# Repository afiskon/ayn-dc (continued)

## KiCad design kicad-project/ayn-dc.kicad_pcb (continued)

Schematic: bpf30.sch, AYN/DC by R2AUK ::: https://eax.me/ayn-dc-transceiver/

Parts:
C65: 1-10p; C_Trim_THD_L7.0mm_W6.5mm_P5.00mm
C66, C69: 100p; C_0805_2012Metric_Pad1.15x1.40mm_HandSolder
C67, C68: 1-30p; C_Trim_THD_L7.0mm_W6.5mm_P5.00mm
D8, D9: 1N4148W; D_SOD-123
K4, K5: G6K-2F-Y; Relay_DPDT_Omron_G6K-2F-Y
Q9: MMBT3904; SOT-23
R67: 4.7K; R_0805_2012Metric_Pad1.15x1.40mm_HandSolder
T6, T7: T37-6; DIP-4_W7.62mm

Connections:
+12V: D8.1 (K), D9.1 (K), K4.1, K5.1; also elsewhere on the board
BPFS: K4.3; also elsewhere on the board
CTL30: R67.2; also elsewhere on the board
GND: C66.2, C67.2, C68.2, C69.2, K4.5, K4.6, K4.7, K5.5, K5.6, K5.7, Q9.2 (E), T6.3, T6.4, T7.3, T7.4; also elsewhere on the board
GND30: D8.2 (A), D9.2 (A), K4.8, K5.8, Q9.3 (C)
unnamed: C65.1, C68.1, C69.1, T7.1
unnamed: C65.2, C66.1, C67.1, T6.2
unnamed: K4.4, T6.1
unnamed: K5.4, T7.2
unnamed: Q9.1 (B), R67.1
SWR_BRIDGE: K5.3; also elsewhere on the board

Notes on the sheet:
5:25T @ T37-6
25:5T @ T37-6

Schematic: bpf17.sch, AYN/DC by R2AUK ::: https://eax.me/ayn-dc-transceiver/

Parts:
C70: 1-10p; C_Trim_THD_L7.0mm_W6.5mm_P5.00mm
C71, C74: 47p; C_0805_2012Metric_Pad1.15x1.40mm_HandSolder
C72, C73: 1-30p; C_Trim_THD_L7.0mm_W6.5mm_P5.00mm
D10, D11: 1N4148W; D_SOD-123
K6, K7: G6K-2F-Y; Relay_DPDT_Omron_G6K-2F-Y
Q10: MMBT3904; SOT-23
R68: 4.7K; R_0805_2012Metric_Pad1.15x1.40mm_HandSolder
T8, T9: T37-6; DIP-4_W7.62mm

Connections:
+12V: D10.1 (K), D11.1 (K), K6.1, K7.1; also elsewhere on the board
BPFS: K6.3; also elsewhere on the board
CTL17: R68.2; also elsewhere on the board
GND: C71.2, C72.2, C73.2, C74.2, K6.5, K6.6, K6.7, K7.5, K7.6, K7.7, Q10.2 (E), T8.3, T8.4, T9.3, T9.4; also elsewhere on the board
GND17: D10.2 (A), D11.2 (A), K6.8, K7.8, Q10.3 (C)
unnamed: C70.1, C73.1, C74.1, T9.1
unnamed: C70.2, C71.1, C72.1, T8.2
unnamed: K6.4, T8.1
unnamed: K7.4, T9.2
unnamed: Q10.1 (B), R68.1
SWR_BRIDGE: K7.3; also elsewhere on the board

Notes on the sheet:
3:19T @ T37-6
19:3T @ T37-6

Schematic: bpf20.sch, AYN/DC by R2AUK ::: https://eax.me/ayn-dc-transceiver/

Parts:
C75: 1-10p; C_Trim_THD_L7.0mm_W6.5mm_P5.00mm
C76, C79: 68p; C_0805_2012Metric_Pad1.15x1.40mm_HandSolder
C77, C78: 1-30p; C_Trim_THD_L7.0mm_W6.5mm_P5.00mm
D12, D13: 1N4148W; D_SOD-123
K8, K9: G6K-2F-Y; Relay_DPDT_Omron_G6K-2F-Y
Q11: MMBT3904; SOT-23
R69: 4.7K; R_0805_2012Metric_Pad1.15x1.40mm_HandSolder
T10, T11: T37-6; DIP-4_W7.62mm

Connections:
+12V: D12.1 (K), D13.1 (K), K8.1, K9.1; also elsewhere on the board
BPFS: K8.3; also elsewhere on the board
CTL20: R69.2; also elsewhere on the board
GND: C76.2, C77.2, C78.2, C79.2, K8.5, K8.6, K8.7, K9.5, K9.6, K9.7, Q11.2 (E), T10.3, T10.4, T11.3, T11.4; also elsewhere on the board
GND20: D12.2 (A), D13.2 (A), K8.8, K9.8, Q11.3 (C)
unnamed: C75.1, C78.1, C79.1, T11.1
unnamed: C75.2, C76.1, C77.1, T10.2
unnamed: K8.4, T10.1
unnamed: K9.4, T11.2
unnamed: Q11.1 (B), R69.1
SWR_BRIDGE: K9.3; also elsewhere on the board

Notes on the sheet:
4:21T @ T37-6
21:4T @ T37-6

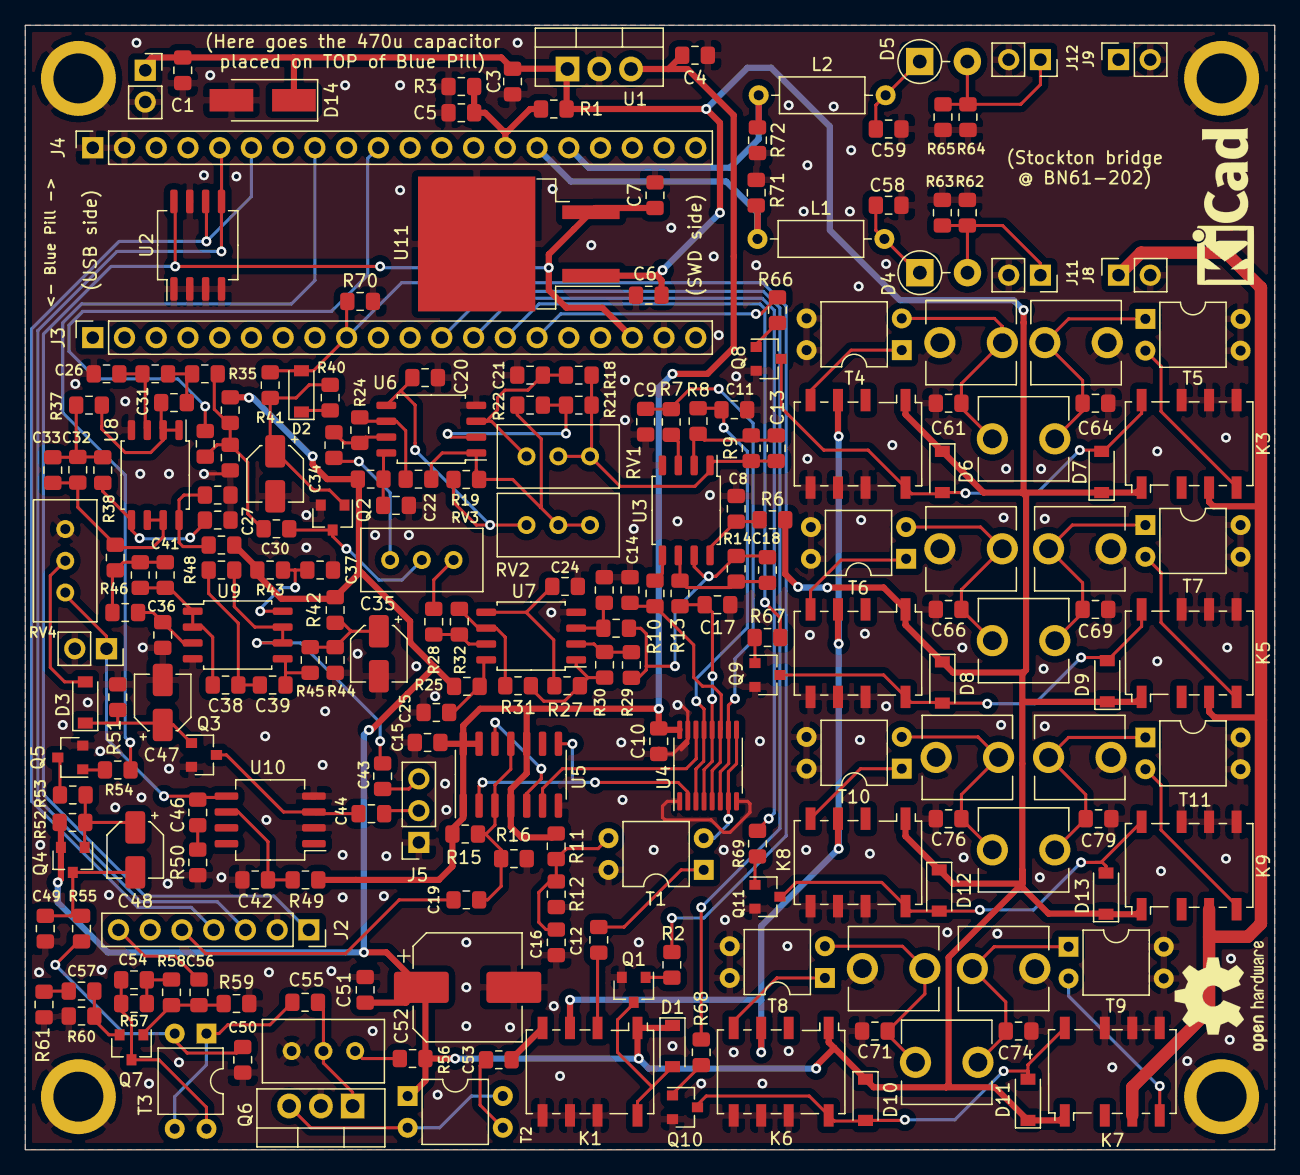
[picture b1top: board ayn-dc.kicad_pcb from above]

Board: 2 copper layers, 100.0 x 90.0 mm, 226 parts (0 on the bottom side), 128 nets.

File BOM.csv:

Reference, Quantity, Value, Footprint
C13 C18 C21 C58 C59 ,5,0.01u,Capacitor_SMD:C_0805_2012Metric_Pad1.15x1.40mm_HandSolder
C2 ,1,470u,Connector_PinSocket_2.54mm:PinSocket_1x02_P2.54mm_Vertical
C23 C31 C46 ,3,0.047u,Capacitor_SMD:C_0805_2012Metric_Pad1.15x1.40mm_HandSolder
C26 C27 C36 ,3,1000p,Capacitor_SMD:C_0805_2012Metric_Pad1.15x1.40mm_HandSolder
C29 C66 C69 ,3,100p,Capacitor_SMD:C_0805_2012Metric_Pad1.15x1.40mm_HandSolder
C3 C6 C24 ,3,0.47u,Capacitor_SMD:C_0805_2012Metric_Pad1.15x1.40mm_HandSolder
C32 C40 ,2,0.033u,Capacitor_SMD:C_0805_2012Metric_Pad1.15x1.40mm_HandSolder
C33 C38 C39 ,3,2200p,Capacitor_SMD:C_0805_2012Metric_Pad1.15x1.40mm_HandSolder
C34 ,1,4.7u,Capacitor_SMD:CP_Elec_4x5.4
C35 C47 ,2,10u,Capacitor_SMD:CP_Elec_4x5.4
C1 C4 C5 C7 C8 C9 C10 C11 C12 C14 C15 C16 C17 C19 C20 C22 C25 C28 C30 C37 C42 C43 C44 C49 C50 C51 C53 C54 C55 C56 C57 ,31,0.1u,Capacitor_SMD:C_0805_2012Metric_Pad1.15x1.40mm_HandSolder
C41 ,1,6800p,Capacitor_SMD:C_0805_2012Metric_Pad1.15x1.40mm_HandSolder
C48 ,1,1u,Capacitor_SMD:CP_Elec_4x5.4
C52 ,1,220u,Capacitor_SMD:CP_Elec_8x10.5
C60 ,1,1-20p,My_Library:C_Trim_THD_L7.0mm_W6.5mm_P5.00mm
C61 C64 ,2,150p,Capacitor_SMD:C_0805_2012Metric_Pad1.15x1.40mm_HandSolder
C62 C63 C67 C68 C72 C73 C77 C78 ,8,1-30p,My_Library:C_Trim_THD_L7.0mm_W6.5mm_P5.00mm
C65 C70 C75 ,3,1-10p,My_Library:C_Trim_THD_L7.0mm_W6.5mm_P5.00mm
C71 C74 ,2,47p,Capacitor_SMD:C_0805_2012Metric_Pad1.15x1.40mm_HandSolder
C76 C79 ,2,68p,Capacitor_SMD:C_0805_2012Metric_Pad1.15x1.40mm_HandSolder
D1 D2 D3 D6 D7 D8 D9 D10 D11 D12 D13 ,11,1N4148W,Diode_SMD:D_SOD-123
D14 ,1,SS14,Diode_SMD:D_SMA_Handsoldering
D4 D5 ,2,1N34 / D311 / etc,Diode_THT:D_DO-41_SOD81_P3.81mm_Vertical_AnodeUp
J2 ,1,Si5351 Module,Connector_PinSocket_2.54mm:PinSocket_1x07_P2.54mm_Vertical
"J3, J4 ",1,Blue Pill,
K1 K2 K3 K4 K5 K6 K7 K8 K9 ,9,G6K-2F-Y or HFD4/12-S,Relay_SMD:Relay_DPDT_Omron_G6K-2F-Y
L1 L2 ,2,1000u,Inductor_THT:L_Axial_L6.6mm_D2.7mm_P10.16mm_Horizontal_Vishay_IM-2
Q1 Q5 Q7 Q8 Q9 Q10 Q11 ,7,MMBT3904,Package_TO_SOT_SMD:SOT-23
Q2 Q3 ,2,MMBF170,Package_TO_SOT_SMD:SOT-23
Q4 ,1,MMBT3906,Package_TO_SOT_SMD:SOT-23
Q6 ,1,RD15HVF1,Package_TO_SOT_THT:TO-220-3_Vertical
R1 R41 ,2,15K,Resistor_SMD:R_0805_2012Metric_Pad1.15x1.40mm_HandSolder
R7 R8 R10 R13 ,4,300,Resistor_SMD:R_0805_2012Metric_Pad1.15x1.40mm_HandSolder
R19 R40 ,2,8.2K,Resistor_SMD:R_0805_2012Metric_Pad1.15x1.40mm_HandSolder
R2 R15 R16 R54 R66 R67 R68 R69 ,8,4.7K,Resistor_SMD:R_0805_2012Metric_Pad1.15x1.40mm_HandSolder
R20 R28 R53 R59 R71 R72 ,6,1K,Resistor_SMD:R_0805_2012Metric_Pad1.15x1.40mm_HandSolder
R21 R22 R23 R24 R29 R30 R31 R32 R57 ,9,3.3K,Resistor_SMD:R_0805_2012Metric_Pad1.15x1.40mm_HandSolder
R26 ,1,5.1K,Resistor_SMD:R_0805_2012Metric_Pad1.15x1.40mm_HandSolder
R27 ,1,4.3K,Resistor_SMD:R_0805_2012Metric_Pad1.15x1.40mm_HandSolder
R3 ,1,2.7K,Resistor_SMD:R_0805_2012Metric_Pad1.15x1.40mm_HandSolder
R35 R36 ,2,33K,Resistor_SMD:R_0805_2012Metric_Pad1.15x1.40mm_HandSolder
R37 R38 ,2,47K,Resistor_SMD:R_0805_2012Metric_Pad1.15x1.40mm_HandSolder
R45 ,1,750K,Resistor_SMD:R_0805_2012Metric_Pad1.15x1.40mm_HandSolder
R46 R47 ,2,36K,Resistor_SMD:R_0805_2012Metric_Pad1.15x1.40mm_HandSolder
R50 ,1,10,Resistor_SMD:R_0805_2012Metric_Pad1.15x1.40mm_HandSolder
R51 ,1,1Meg,Resistor_SMD:R_0805_2012Metric_Pad1.15x1.40mm_HandSolder
R52 ,1,470,Resistor_SMD:R_0805_2012Metric_Pad1.15x1.40mm_HandSolder
R56 ,1,2.2K,Resistor_SMD:R_0805_2012Metric_Pad1.15x1.40mm_HandSolder
R58 ,1,1.3K,Resistor_SMD:R_0805_2012Metric_Pad1.15x1.40mm_HandSolder
R6 R17 R25 R33 R43 R49 R55 ,7,22,Resistor_SMD:R_0805_2012Metric_Pad1.15x1.40mm_HandSolder
R60 ,1,68,Resistor_SMD:R_0805_2012Metric_Pad1.15x1.40mm_HandSolder
R61 ,1,6,Resistor_SMD:R_0805_2012Metric_Pad1.15x1.40mm_HandSolder
R62 R63 R64 R65 ,4,100,Resistor_SMD:R_0805_2012Metric_Pad1.15x1.40mm_HandSolder
R70 ,1,100K,Resistor_SMD:R_0805_2012Metric_Pad1.15x1.40mm_HandSolder
R9 R11 R12 R14 R18 R34 R39 R42 R44 R48 ,10,10K,Resistor_SMD:R_0805_2012Metric_Pad1.15x1.40mm_HandSolder
RV1 RV2 ,2,50K,Potentiometer_THT:Potentiometer_Bourns_3296W_Vertical
RV3 ,1,500,Potentiometer_THT:Potentiometer_Bourns_3296W_Vertical
RV4 RV5 ,2,10K,Potentiometer_THT:Potentiometer_Bourns_3296W_Vertical
T1 T2 T3 ,3,FT37-43,Package_DIP:DIP-4_W7.62mm
T4 T5 T6 T7 T8 T9 T10 T11 ,8,T37-6,Package_DIP:DIP-4_W7.62mm
U1 ,1,L7805,Package_TO_SOT_THT:TO-220-3_Vertical
U10 ,1,LM386,Package_SO:SO-8_5.3x6.2mm_P1.27mm
U11 ,1,L7805,Package_TO_SOT_SMD:TO-263-2
U2 ,1,24LC64,Package_SO:SO-8_5.3x6.2mm_P1.27mm
U3 U6 U7 U8 U9 ,5,NE5532,Package_SO:SOIC-8_5.23x5.23mm_P1.27mm
U4 ,1,FST3253,Package_SO:TSSOP-16_4.4x5mm_P0.65mm
U5 ,1,74AC74,Package_SO:SOIC-14_3.9x8.7mm_P1.27mm
J8 J9 J11 J12,1,BN61-202,
J6,2,220u,"Through-hole capacitors, ideally 8 mm diameter"

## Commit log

2022-12-03 Move the project from a sandbox repository
2022-12-03 Remove DNP components from the BOM
2022-12-04 Increase the speed of the I2C bus
2022-12-04 Add BN61-202 and 2x 220u capacitors to the BOM
2022-12-04 BOM: list HFD4/12S as a possible substitute to G6K-2F-Y
2022-12-04 FW: display the voltage a bit more accurately
2022-12-05 Add a comment about masking spurs
2022-12-05 Minor silkscreen + F_Fab layer fixes
2022-12-06 Add a 3D-printable desktop stand model
2022-12-07 Rename desktop-stand/ to stl-files/
2022-12-07 Add dust-sover.{scad,stl}
2022-12-12 Add a bit more GND vias; update gerber.zip
2022-12-21 FW: continue working even if EEPROM is missing
2022-12-21 Experiment: move I2C away from 5V bus, use PB10/PB11 (SCL/SDA)
2022-12-21 Fix buttonLockPressed()
2022-12-21 Use PB0 for ENABLE_CW_TONE and PA10 for LOCK_BTN
2022-12-21 HW: use 5V_DIGITAL and move I2C away from 5V bus
2022-12-21 HW: minor changes
2022-12-21 FW: Nov 2022 -> Dec 2022
2022-12-21 ayn-dc-schematic.pdf rev3
2022-12-21 ayn-dc-F_Fab.pdf rev3
2022-12-21 BOM rev3
2022-12-21 gerber.zip rev3
2022-12-21 ayn-dc-schematic.pdf rev3, color version
2022-12-21 rev3: minor silkscreen fix
2022-12-28 Update si5351 correction for a new board
2022-12-29 Use a pull-up resistor @ PA10 (LOCK btn)
2022-12-29 Hide spurs in my item
